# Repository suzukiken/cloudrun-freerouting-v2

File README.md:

For Local Docker
```
docker build -t freeroutingv2 .
docker run -it --rm freeroutingv2 bash
java -jar freerouting-2.0.1.jar -de /opt/sample.dsn -do /opt/output.ses --gui.enabled=false
java -jar freerouting-2.0.1.jar --gui.enabled=false -de test/pcb.dsn -do test/pcb.ses -dr test/pcb.rules -mp 1000
docker run -it --rm -p 8080:8080 freeroutingv2
```

For GCP CloudRun:
```
docker build . -t freeroutingv2 --platform linux/amd64 && \
docker tag freeroutingv2 asia-northeast1-docker.pkg.dev/firstcloudrun-323509/v2/freeroutingv2:latest && \
gcloud auth configure-docker asia-northeast1-docker.pkg.dev && \
docker push asia-northeast1-docker.pkg.dev/firstcloudrun-323509/v2/freeroutingv2:latest
gcloud run deploy --image asia-northeast1-docker.pkg.dev/firstcloudrun-323509/v2/freeroutingv2:latest --allow-unauthenticated --memory 2Gi --concurrency 1 --timeout=600
gcloud run services update-traffic freeroutingv2 --to-latest
```

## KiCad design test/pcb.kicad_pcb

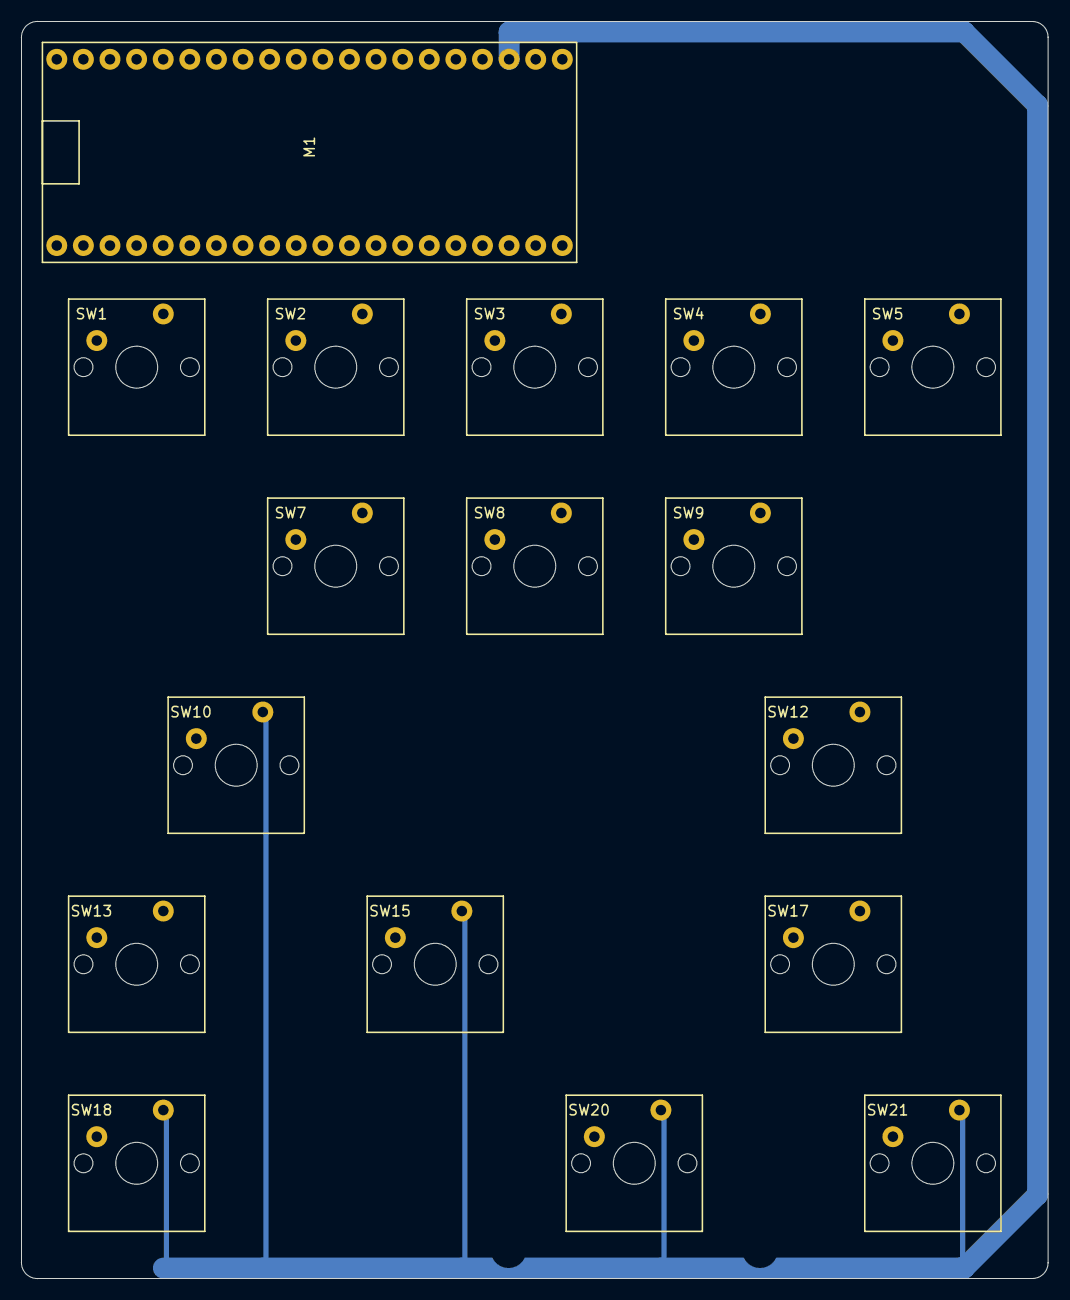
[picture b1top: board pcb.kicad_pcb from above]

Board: 2 copper layers, 98.0 x 120.0 mm, 17 parts (0 on the bottom side), 17 nets.

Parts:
M1: RasPiPico; pipico
SW1, SW2, SW3, SW4, SW5, SW7, SW8, SW9, SW12, SW13, SW15, SW17, SW18, SW21: SW_Push; keyswitch
SW10, SW20: SW_Push; keyswitch-with-stabilizer

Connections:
GND4: M1.23, SW1.2, SW2.2, SW3.2, SW4.2, SW5.2, SW7.2, SW8.2, SW9.2, SW10.2, SW12.2, SW13.2, SW15.2, SW17.2, SW18.2, SW20.2, SW21.2
GP0: M1.1, SW18.1
GP1: M1.2, SW13.1
GP2: M1.4, SW1.1
GP6: M1.9, SW10.1
GP7: M1.10, SW7.1
GP8: M1.11, SW2.1
GP11: M1.15, SW15.1
GP12: M1.16, SW8.1
GP13: M1.17, SW3.1
GP17: M1.22, SW5.1
GP18: M1.24, SW12.1
GP19: M1.25, SW17.1
GP20: M1.26, SW21.1
GP26: M1.31, SW4.1
GP27: M1.32, SW9.1
GP28: M1.34, SW20.1

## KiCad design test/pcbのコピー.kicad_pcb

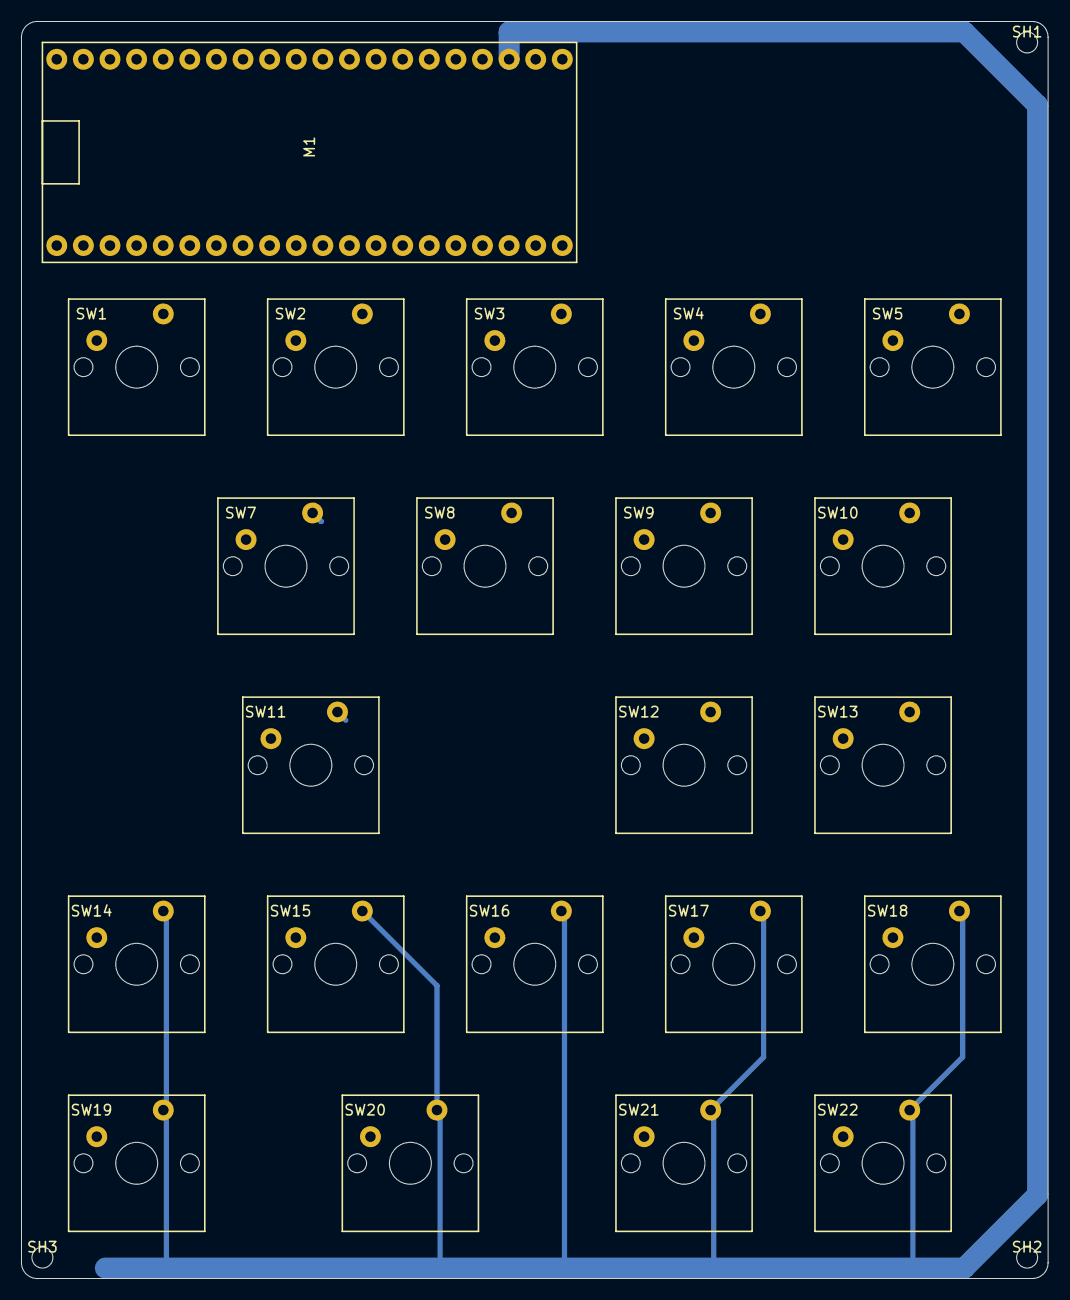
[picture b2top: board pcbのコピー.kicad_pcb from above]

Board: 2 copper layers, 98.0 x 120.0 mm, 25 parts (0 on the bottom side), 22 nets.

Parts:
M1: RasPiPico; pipico
SH1, SH2, SH3: SCREW_HOLE; screwhole
SW1, SW2, SW3, SW4, SW5, SW7, SW8, SW9, SW10, SW12, SW13, SW14, SW15, SW16, SW17, SW18, SW19, SW20, SW21, SW22: SW_Push; keyswitch
SW11: SW_Push; keyswitch-with-stabilizer

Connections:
GND4: M1.23, SW1.2, SW2.2, SW3.2, SW4.2, SW5.2, SW7.2, SW8.2, SW9.2, SW10.2, SW11.2, SW12.2, SW13.2, SW14.2, SW15.2, SW16.2, SW17.2, SW18.2, SW19.2, SW20.2, SW21.2, SW22.2
GP0: M1.1, SW19.1
GP1: M1.2, SW14.1
GP4: M1.6, SW1.1
GP5: M1.7, SW20.1
GP6: M1.9, SW15.1
GP7: M1.10, SW11.1
GP8: M1.11, SW7.1
GP9: M1.12, SW2.1
GP11: M1.15, SW16.1
GP13: M1.17, SW8.1
GP14: M1.19, SW3.1
GP16: M1.21, SW5.1
GP17: M1.22, SW10.1
GP18: M1.24, SW13.1
GP19: M1.25, SW18.1
GP20: M1.26, SW22.1
GP21: M1.27, SW4.1
GP22: M1.29, SW9.1
GP26: M1.31, SW12.1
GP27: M1.32, SW17.1
GP28: M1.34, SW21.1

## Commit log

2025-04-05 first
2025-04-05 update test
2025-05-01 add freerouting 2.1.0
2025-05-01 Add support for selecting JAR version via URL path
2025-05-01 Add GitHub Actions workflow for Cloud Run deployment
2025-06-17 fix file size 0
